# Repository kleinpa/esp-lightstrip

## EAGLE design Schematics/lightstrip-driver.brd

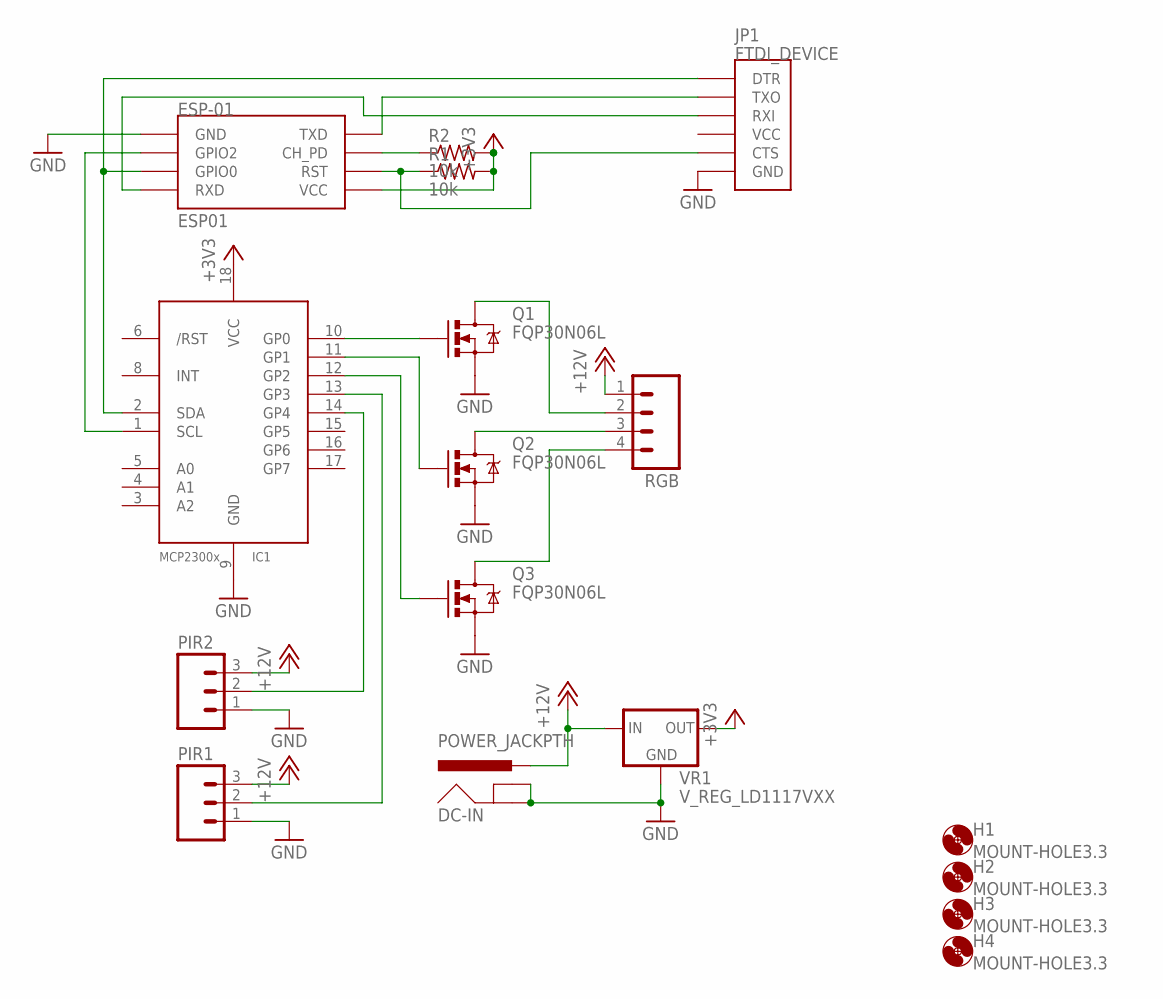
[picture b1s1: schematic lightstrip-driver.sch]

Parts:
DC-IN: POWER_JACKPTH; POWER_JACK_PTH
ESP-01: ESP01
H1, H2, H3, H4: MOUNT-HOLE3.3; 3,3
IC1: MCP2300X/P; DIL18
JP1: FTDI_DEVICE; FTDI_DEVICE_SIDE
PIR1, PIR2: M03PTH; 1X03
Q1, Q2, Q3: FQP30N06L; TO220V
R1, R2: 10k; 0207/7
RGB: M04PTH; 1X04
VR1: V_REG_LD1117VXX; 78XXL

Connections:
+3V3: ESP-01.VCC, IC1.18 (VCC), R1.2, R2.2, VR1.GND (OUT)
+12V: DC-IN.PWR, PIR1.3, PIR2.3, RGB.1, VR1.OUT (IN)
GND: DC-IN.GND, DC-IN.GNDBREAK, ESP-01.GND, IC1.9 (GND), JP1.P$6 (GND), PIR1.1, PIR2.1, Q1.3 (S), Q2.3 (S), Q3.3 (S), VR1.IN (GND)
unnamed: IC1.13 (GP3), PIR1.2
unnamed: ESP-01.GPIO2, IC1.1 (SCL)
unnamed: ESP-01.CH_PD, R2.1
unnamed: IC1.10 (GP0), Q1.1 (G)
unnamed: IC1.11 (GP1), Q2.1 (G)
unnamed: IC1.12 (GP2), Q3.1 (G)
unnamed: ESP-01.RX (RXD), JP1.P$3 (RXI)
unnamed: Q1.2 (D), RGB.2
unnamed: ESP-01.TX (TXD), JP1.P$2 (TXO)
unnamed: Q2.2 (D), RGB.3
unnamed: Q3.2 (D), RGB.4
unnamed: IC1.14 (GP4), PIR2.2
unnamed: ESP-01.GPIO0, IC1.2 (SDA), JP1.P$1 (DTR)
unnamed: ESP-01.RST, JP1.P$5 (CTS), R1.1

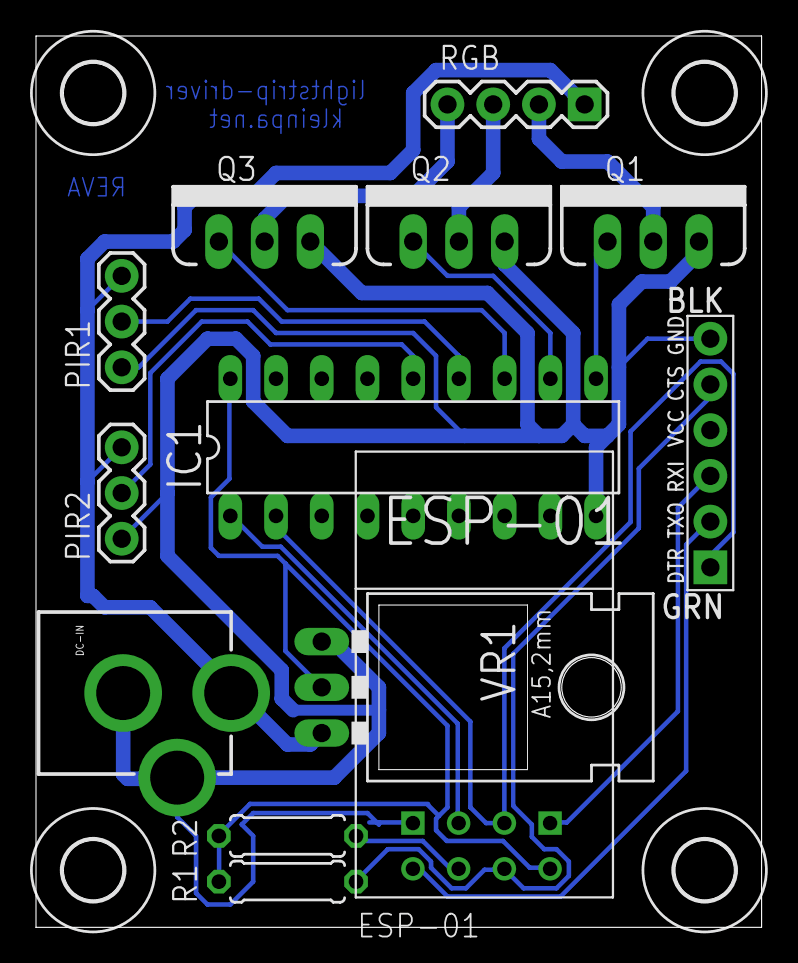
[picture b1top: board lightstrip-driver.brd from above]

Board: 2 copper layers, 40.3 x 49.5 mm, 17 parts (0 on the bottom side), 17 nets.

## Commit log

2015-05-21 Update board with correct ESP8266 autoreset connections
2015-05-22 Add mounting holes

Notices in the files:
parts and their libraries:
SparkFun-Connectors: Licensing: Creative Commons ShareAlike 4.0 International - https://creativecommons.org/licenses/by-sa/4.0
